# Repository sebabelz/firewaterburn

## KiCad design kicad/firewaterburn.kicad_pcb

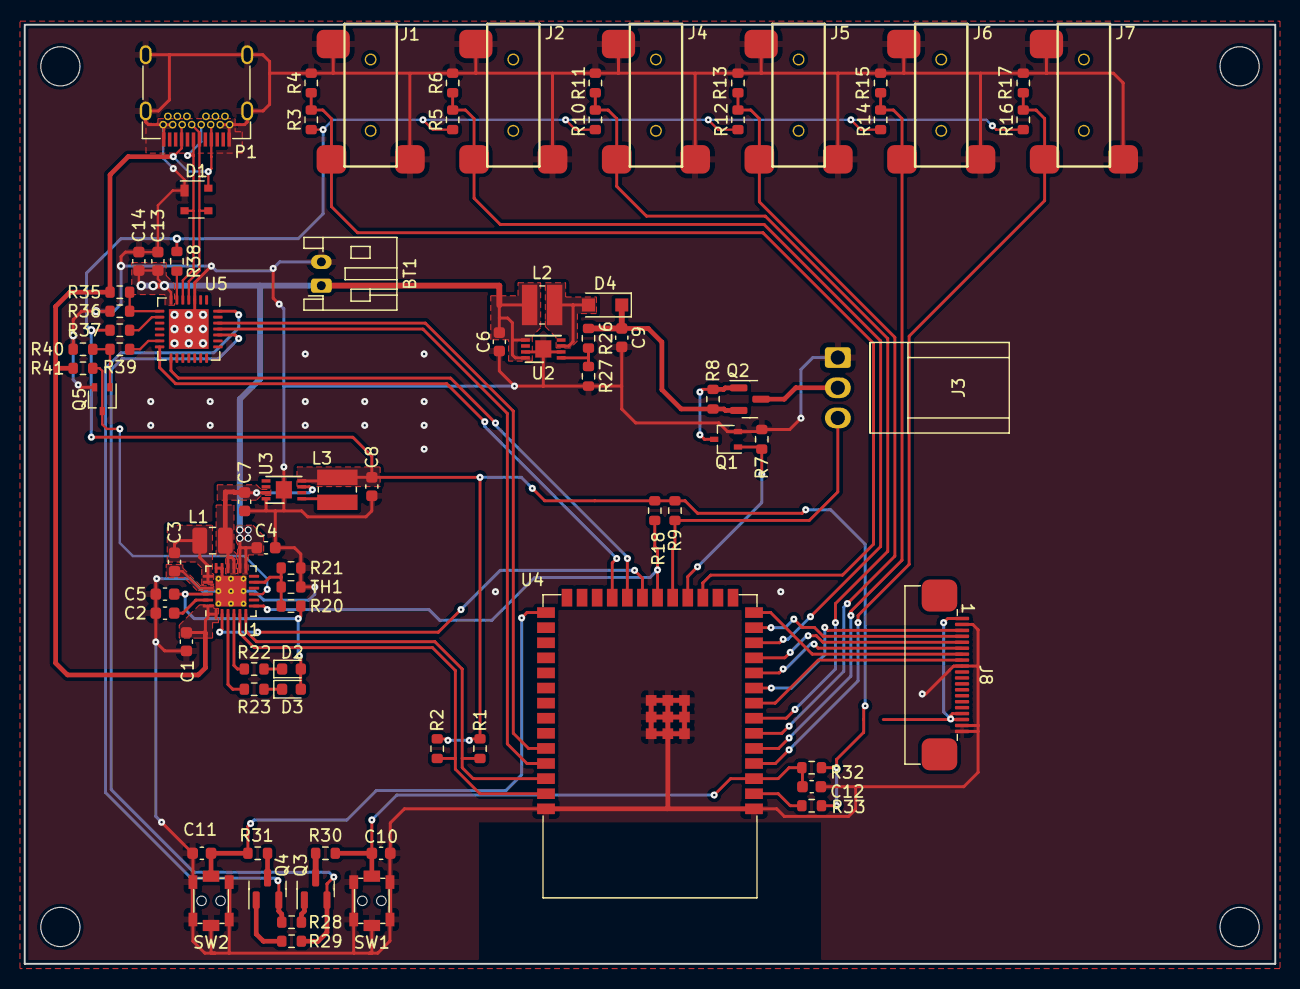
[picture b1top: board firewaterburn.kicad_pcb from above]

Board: 2 copper layers, 105.2 x 79.0 mm, 81 parts (0 on the bottom side), 59 nets.

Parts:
BT1: Battery_Cell; JST_PH_S2B-PH-K_1x02_P2.00mm_Horizontal
C1: 1µ; C_0603_1608Metric
C2, C4, C6, C9: 10µ; C_0603_1608Metric
C3: 47nF; C_0603_1608Metric
C5, C7, C8, C13: 4,7µ; C_0603_1608Metric
C10, C11, C12, C14: 100n; C_0603_1608Metric
D1: SP0503BAHTG; SOT-143
D2, D3: LED; LED_0603_1608Metric
D4: PMEG4010ER; D_SOD-123F
J1, J2, J4, J5, J6, J7: AudioJack2_SwitchT; MJ-2523
J3: Conn_01x03; Molex_KK-254_AE-6410-03A_1x03_P2.54mm_Vertical
J8: R61529 LCD; FPC_BOTTOM_20POS_Würth_68712014522
L1: 1µ; L_1008_2520Metric
L2, L3: 4µ7; L_Wuerth_MAPI-3015
P1: USB_C_Plug_USB2.0; USB_C_Receptacle_Amphenol_12401548E4-2A
Q1: DMN61D9UWQ-13; SOT-323_SC-70
Q2: DMP31D0U-7; SOT-23
Q3, Q4: SS8050-G; SOT-23
Q5: DMN2004WK-7; SOT-323_SC-70
R1, R2: 1k; R_0603_1608Metric
R3, R5, R10, R12, R14, R16: 4k42; R_0603_1608Metric
R4, R6, R11, R13, R15, R17: 3k4; R_0603_1608Metric
R7, R8: 4k7; R_0603_1608Metric
R9, R18, R28, R29, R32, R41: 10k; R_0603_1608Metric
R20: 5k23; R_0603_1608Metric
R21: 30k1; R_0603_1608Metric
R22, R23: 2k2; R_0603_1608Metric
R26: 1050k; R_0603_1608Metric
R27: 120k; R_0603_1608Metric
R30, R31, R33, R38, R39: 0R; R_0603_1608Metric
R35: 22k1; R_0603_1608Metric
R36: 47k5; R_0603_1608Metric
R37: 2k; R_0603_1608Metric
R40: 1M; R_0603_1608Metric
SW1, SW2: SW_MEC_5G; PTS820J25MSMTRLFS
TH1: NTCG163JH103JT1; R_0603_1608Metric
U1: RT9471GQW; WQFN-24-1EP_4x4mm_P0.5mm_EP2.6x2.6mm_ThermalVias
U2: MCP1663T-E/MNY; DFN-8-1EP_3x2mm_P0.5mm_EP1.36x1.46mm
U3: MCP1603-330I/MC; DFN-8-1EP_3x2mm_P0.5mm_EP1.36x1.46mm
U4: ESP32-S3-Rx; ESP32-S3-WROOM-1
U5: CP2102N-Axx-xQFN28; QFN-28-1EP_5x5mm_P0.5mm_EP3.35x3.35mm

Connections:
+3V3: C8.1, J8.1 (VDD), J8.17 (BLVDD), J8.18 (BLVDD), L3.2, R1.1, R2.1, R3.1, R5.1, R9.1, R10.1, R12.1, R14.1, R16.1, R18.2, R32.1, R33.2, R37.1, R38.1, U3.4 (VFB)
+12V: C9.1, D4.1 (K), Q2.2 (S), R8.1, R26.1
/OUTPUT/PWM: Q1.1 (G), R7.1, U4.18 (IO10)
/OUTPUT/TACHO: J3.3, R9.2, U4.19 (IO11)
/OUTPUT/probe1: J1.T, R3.2, R4.1, U4.17 (IO9)
/OUTPUT/probe2: J4.T, R10.2, R11.1, U4.7 (IO7)
/OUTPUT/probe3: J6.T, R14.2, R15.1, U4.5 (IO5)
/OUTPUT/probe4: J2.T, R5.2, R6.1, U4.12 (IO8)
/OUTPUT/probe5: J5.T, R12.2, R13.1, U4.6 (IO6)
/OUTPUT/probe6: J7.T, R16.2, R17.1, U4.4 (IO4)
/USB<->UART/CHR0: U4.22 (IO14), U5.15 (CHR0)
/USB<->UART/CHR1: U4.23 (IO21), U5.14 (CHR1)
/USB<->UART/CHREN: Q5.3 (D), R41.1, U1.9 (~CE)
/USB<->UART/CHREN_: R39.2, U5.13 (CHREN)
/USB<->UART/D+: D1.3 (K), P1.A6 (D+), P1.B6 (D+), U5.4 (D+)
/USB<->UART/D-: D1.2 (K), P1.A7 (D-), P1.B7 (D-), U5.5 (D-)
/USB<->UART/DTS: Q4.2 (E), R28.2, U5.28 (~DTR)
/USB<->UART/RXD: U4.37 (TXD0), U5.25 (RXD)
/USB<->UART/TXD: U4.36 (RXD0), U5.26 (TXD)
/mcu_n_tft/BOOT: C11.2, R31.1, SW2.2 (B), U4.27 (IO0)
/mcu_n_tft/CHR_INT: R18.1, U1.7 (~INT), U4.20 (IO12)
/mcu_n_tft/CHR_PSEL: U1.2 (PSEL), U4.21 (IO13)
/mcu_n_tft/EN: C10.2, C12.1, R30.1, R32.2, SW1.2 (B), U4.3 (EN)
/mcu_n_tft/RTS: Q3.2 (E), R29.2, U5.24 (~RTS)
/mcu_n_tft/SCL: R2.2, U1.5 (SCL), U4.39 (IO1)
/mcu_n_tft/SDA: R1.2, U1.6 (SDA), U4.38 (IO2)
/mcu_n_tft/SPICLK: J8.3 (SPI_SCLK), U4.9 (IO16)
/mcu_n_tft/SPICS0: J8.6 (SPI_CS), U4.10 (IO17)
/mcu_n_tft/SPID: J8.5 (SPI_MOSI), U4.11 (IO18)
/mcu_n_tft/SPIQ: J8.4 (SPI_MISO), U4.13 (IO19)
/mcu_n_tft/~INT: J8.7 (~INT), U4.14 (IO20)
/mcu_n_tft/~PD: J8.8 (~PD), U4.8 (IO15)
/power unit/STAT: R22.2, U1.4 (STAT)
/power unit/~PG: R23.2, U1.3 (~PG)
GND: BT1.2 (-), C1.2, C2.2, C4.2, C5.2, C6.2, C7.2, C8.2, C9.2, C10.1, C11.1, C12.2, C13.2, C14.2, D1.1 (A), J1.S, J1.TN, J2.S, J2.TN, J3.1, J4.S, J4.TN, J5.S, J5.TN, J6.S, J6.TN, J7.S, J7.TN, J8.2 (GND), J8.9 (MODE), J8.19 (BLGND), J8.20 (BLGND), P1.1 (GND), P1.2 (GND), P1.A1 (GND), P1.A12 (GND), P1.B1 (GND), P1.B12 (GND), P1.S1 (SHIELD), Q1.2 (S), Q5.2 (S), R4.2, R6.2, R7.2, R11.2, R13.2, R15.2, R17.2, R21.2, R27.2, R36.2, R40.1, SW1.1 (A), SW1.3 (GND), SW2.1 (A), SW2.3 (GND), TH1.2, U1.17 (GND), U1.18 (GND), U1.25 (GND), U2.2 (GND), U2.7 (GND), U2.9 (GND), U3.8 (GND), U3.9 (GND), U4.1 (GND), U4.40 (GND), U4.41 (GND), U5.3 (GND), U5.29 (GND)
unnamed: C2.1, U1.23 (PMID)
unnamed: C3.1, U1.21 (BTST)
unnamed: C3.2, L1.1, U1.19 (SW), U1.20 (SW)
unnamed: C5.1, D2.2 (A), D3.2 (A), R20.1, U1.22 (REGN)
unnamed: D2.1 (K), R22.1
unnamed: D3.1 (K), R23.1
unnamed: D4.2 (A), L2.2, U2.3 (SW)
unnamed: J3.2, Q2.3 (D)
unnamed: L3.1, U3.1 (L_{x})
unnamed: Q1.3 (D), Q2.1 (G), R8.2
unnamed: Q3.1 (B), R28.1
unnamed: Q3.3 (C), R30.2
unnamed: Q4.1 (B), R29.1
unnamed: Q4.3 (C), R31.2
unnamed: Q5.1 (G), R39.1, R40.2
unnamed: R20.2, R21.1, TH1.1, U1.11 (TS)
unnamed: R26.2, R27.1, U2.1 (VFB)
unnamed: R33.1, U4.2 (3V3)
unnamed: R35.2, R36.1, U5.8 (VBUS)
unnamed: R37.2, U5.9 (~RST)
unnamed: R38.2, U5.6 (VDD)
VAA: BT1.1 (+), C4.1, C6.1, C13.1, C14.1, L2.1, U1.13 (BAT), U1.14 (BAT), U2.5 (VIN), U2.8 (EN), U5.7 (VREGIN)
VBUS: C1.1, D1.4 (K), P1.A4 (VBUS), P1.A9 (VBUS), P1.B4 (VBUS), P1.B9 (VBUS), R35.1, R41.2, U1.1 (VAC), U1.24 (VBUS)
VS: C7.1, L1.2, U1.15 (SYS), U1.16 (SYS), U3.3 (~SHDN), U3.7 (VIN)

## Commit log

2022-04-02 remove Rx with 0 Ohms
2022-04-19 add CommandBuffer
2022-04-20 Add fix for CommandBuffer to get the correct transaction length
2022-04-26 rename AdcProbe
